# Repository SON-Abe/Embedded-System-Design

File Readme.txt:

Student Name: Abraham Garcia

Student #: 5005262049

Student Email: garci11@unlv.nevada.edu

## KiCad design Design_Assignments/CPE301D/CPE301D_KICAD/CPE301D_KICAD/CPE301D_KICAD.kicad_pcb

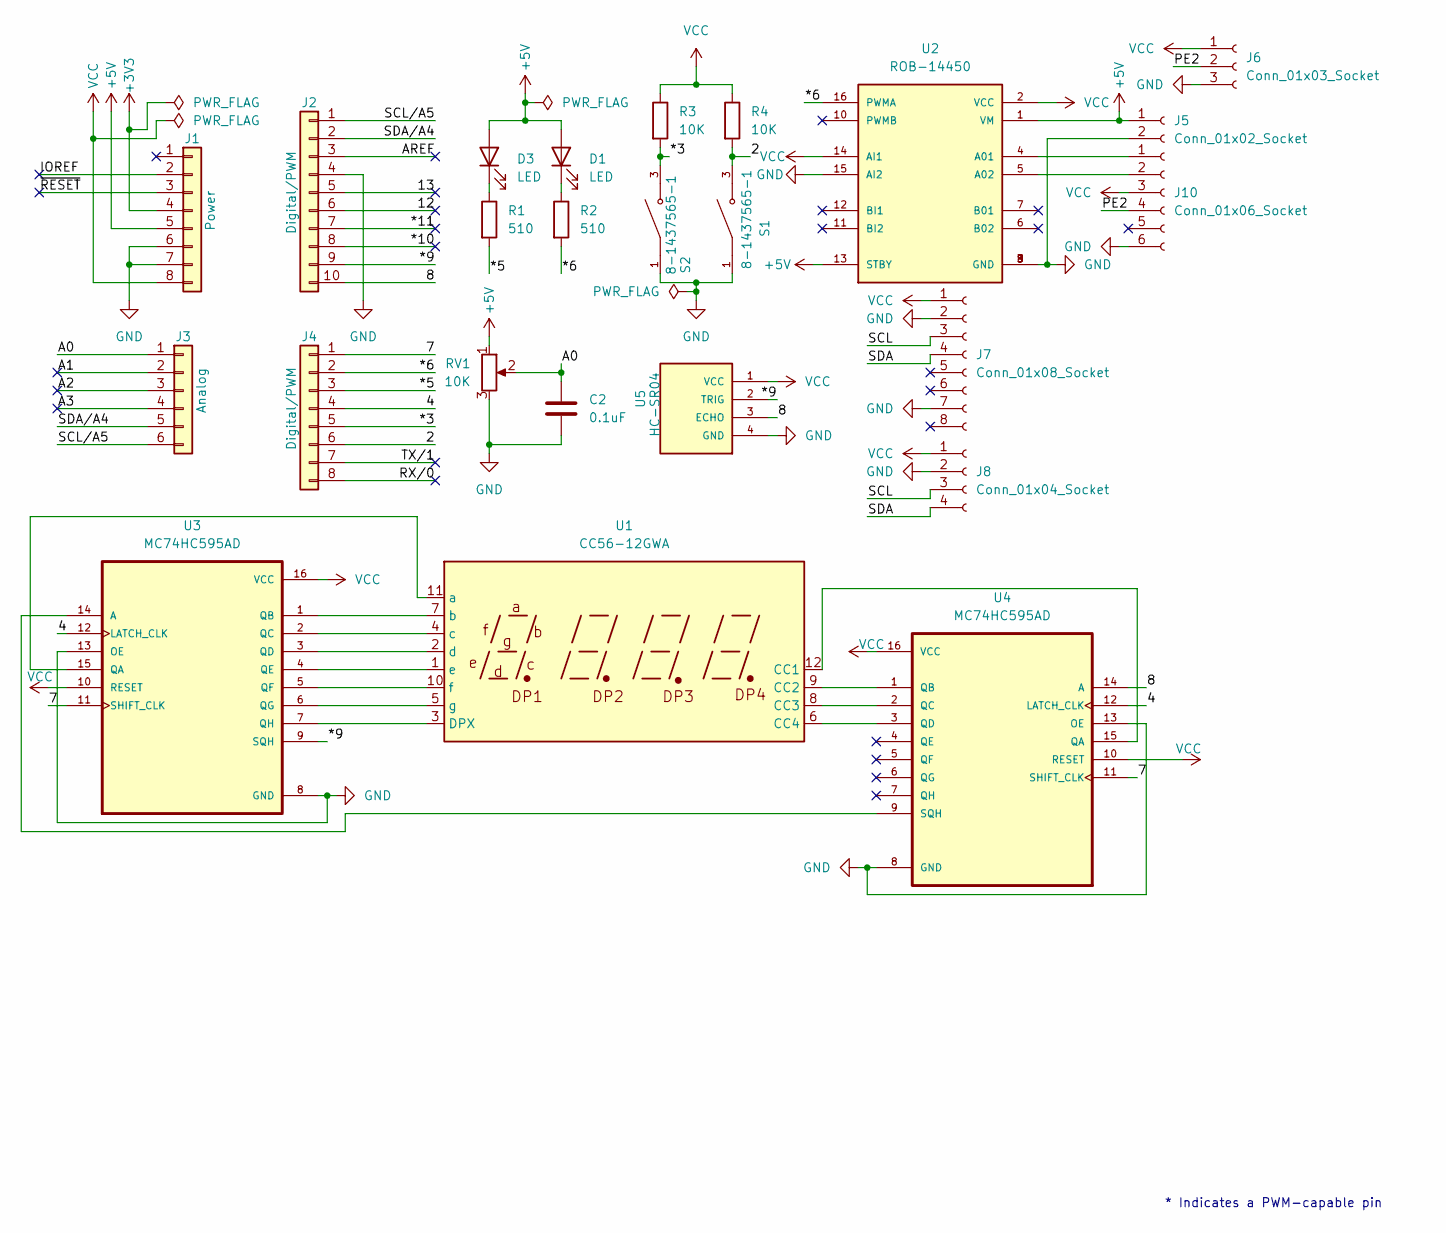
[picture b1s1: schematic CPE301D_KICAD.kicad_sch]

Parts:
C2: 0.1uF; C_Axial_L3.8mm_D2.6mm_P7.50mm_Horizontal
D1, D3: LED; LED_D3.0mm_FlatTop
J1: Power; PinSocket_1x08_P2.54mm_Vertical
J2: Digital/PWM; PinSocket_1x10_P2.54mm_Vertical
J3: Analog; PinSocket_1x06_P2.54mm_Vertical
J4: Digital/PWM; PinSocket_1x08_P2.54mm_Vertical
J5: Conn_01x02_Socket; JST_ZE_B02B-ZESK-1D_1x02_P1.50mm_Vertical
J6: Conn_01x03_Socket; JST_ZE_B03B-ZESK-D_1x03_P1.50mm_Vertical
J7: Conn_01x08_Socket; JST_ZE_B08B-ZESK-D_1x08_P1.50mm_Vertical
J8: Conn_01x04_Socket; JST_ZE_B04B-ZESK-D_1x04_P1.50mm_Vertical
J10: Conn_01x06_Socket; JST_ZE_B06B-ZESK-D_1x06_P1.50mm_Vertical
R1, R2: 510; R_Axial_DIN0204_L3.6mm_D1.6mm_P1.90mm_Vertical
R3, R4: 10K; R_Axial_DIN0204_L3.6mm_D1.6mm_P1.90mm_Vertical
RV1: 10K; Potentiometer_Bourns_3269P_Horizontal
S1, S2: 8-1437565-1; SW_8-1437565-1; PARTREV H3
U1: CC56-12GWA
U2: ROB-14450; MODULE_ROB-14450; PARTREV 11-13-17; DigiKey_Part_Number 1568-1755-ND
U3, U4: MC74HC595AD; SOIC127P600X175-16N
U5: HC-SR04; XCVR_HC-SR04

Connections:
+3V3: J1.4
+5V: D1.2 (A), D3.2 (A), J1.5, J5.1, RV1.1, U2.1 (VM), U2.13 (STBY)
/2: J4.6, R4.2, S1.3
/4: J4.4, U3.12 (LATCH_CLK), U4.12 (LATCH_CLK)
/7: J4.1, U3.11 (SHIFT_CLK), U4.11 (SHIFT_CLK)
/8: J2.10, U4.14 (A), U5.3 (ECHO)
/12: J2.6
/13: J2.5
/*3: J4.5, R3.2, S2.3
/*5: J4.3, R1.2
/*6: J4.2, R2.2, U2.16 (PWMA)
/*9: J2.9, U3.9 (SQH), U5.2 (TRIG)
/*10: J2.8
/*11: J2.7
/A0: C2.1, J3.1, RV1.2
/A1: J3.2
/A2: J3.3
/A3: J3.4
/AREF: J2.3
/IOREF: J1.2
/PE2: J6.2, J10.4
/RX/0: J4.8
/SCL: J7.3, J8.3
/SCL/A5: J2.1, J3.6
/SDA: J7.4, J8.4
/SDA/A4: J2.2, J3.5
/TX/1: J4.7
/~RESET: J1.3
GND: C2.2, J1.6, J1.7, J2.4, J5.2, J6.3, J7.2, J7.7, J8.2, J10.6, RV1.3, S1.1, S2.1, U2.3 (GND), U2.8 (GND), U2.9 (GND), U2.15 (AI2), U3.8 (GND), U3.13 (OE), U4.8 (GND), U4.13 (OE), U5.4 (GND)
unnamed: D1.1 (K), R2.1
unnamed: D3.1 (K), R1.1
unnamed: J10.1, U2.4 (A01)
unnamed: J10.2, U2.5 (A02)
unnamed: U1.12 (CC1), U4.15 (QA)
unnamed: U1.9 (CC2), U4.1 (QB)
unnamed: U1.8 (CC3), U4.2 (QC)
unnamed: U1.6 (CC4), U4.3 (QD)
unnamed: U1.3 (DPX), U3.7 (QH)
unnamed: U1.11 (a), U3.15 (QA)
unnamed: U1.7 (b), U3.1 (QB)
unnamed: U1.4 (c), U3.2 (QC)
unnamed: U1.2 (d), U3.3 (QD)
unnamed: U1.1 (e), U3.4 (QE)
unnamed: U1.10 (f), U3.5 (QF)
unnamed: U1.5 (g), U3.6 (QG)
unnamed: U3.14 (A), U4.9 (SQH)
VCC: J1.8, J6.1, J7.1, J8.1, J10.3, R3.1, R4.1, U2.2 (VCC), U2.14 (AI1), U3.10 (RESET), U3.16 (VCC), U4.10 (RESET), U4.16 (VCC), U5.1 (VCC)

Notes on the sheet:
* Indicates a PWM-capable pin

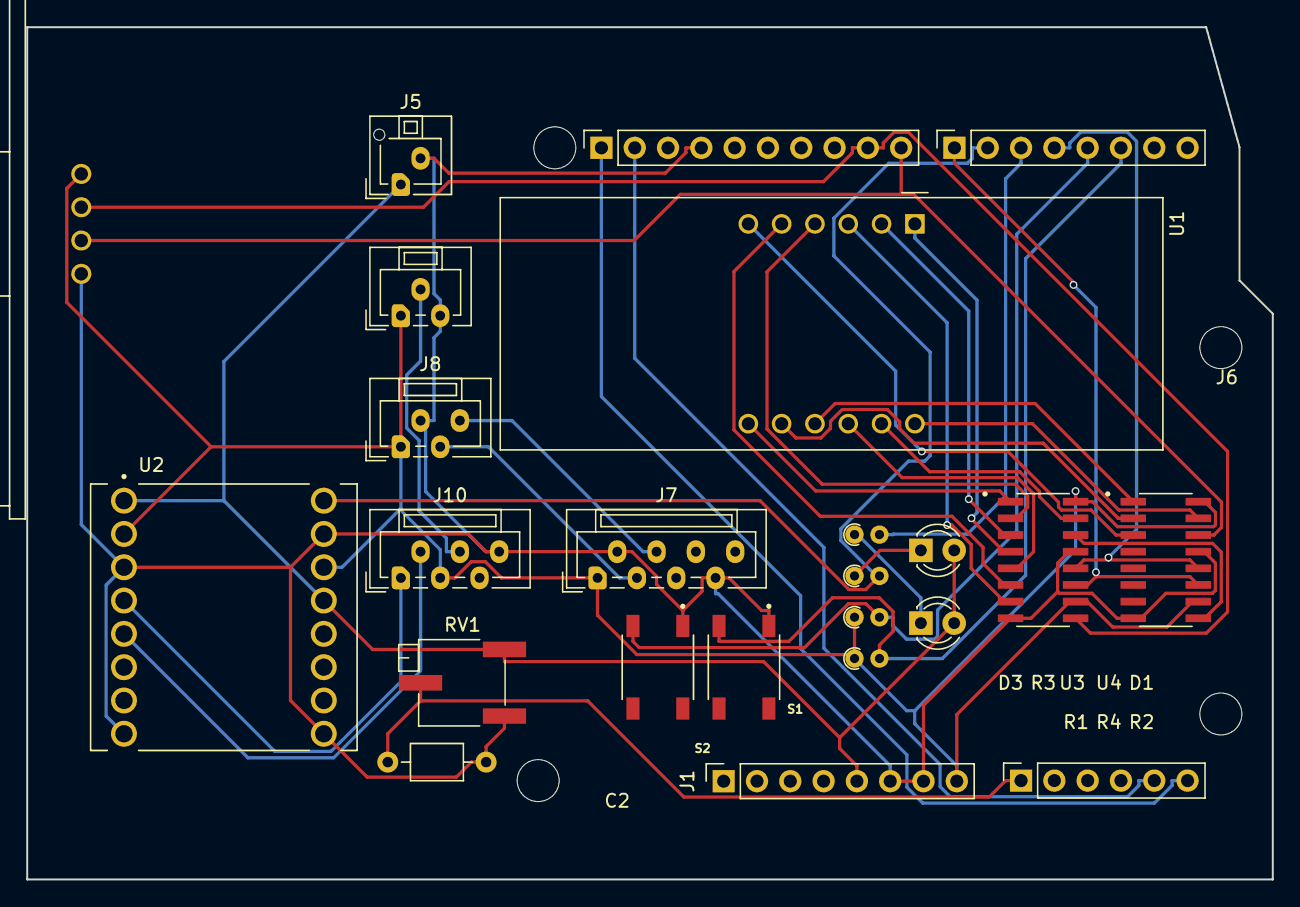
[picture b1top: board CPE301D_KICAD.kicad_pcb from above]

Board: 2 copper layers, 95.0 x 65.0 mm, 28 parts (0 on the bottom side), 34 nets.

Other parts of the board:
MH1, MH2, MH3, MH4: MountingHole_3.2mm

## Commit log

2024-02-18 Design Example Upload Demo
2024-02-26 DA1 Abraham Garcia LAB01
2024-02-26 LAB01_DA1
2024-04-14 DA4_Abraham_Garcia
2024-04-22 DA05
2024-05-05 Create DA6
